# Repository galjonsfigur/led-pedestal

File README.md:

# LED Pedestal

This repository contains hardware, firmware and
3D-printable case for the LED Pedestal project.

## What is this project?

The name says it all - it's just a fancy-looking circuit
that can blink your precious (retro or not) LED that you probably
still keep at the bottom of your component drawer. The circuit is heavily
over-complicated and the same thing could be done using 3 or 4 components total,
but it looks cool and has some nice features:

- PIC10F222 micro controller with sophisticated firmware (as far as 512 bytes 
firmware written in C with some assembly can be)
- Whole 3 (three!) randomly-parameterized LED effects to select from 
- Micro USB for charging the Li-Ion battery with all the (unnecessary)
protection circuits (overcharge, over-discharge and short-circuit protection) 
- small button for checking battery level and changing LED Blinking modes
- reaction to connecting charger and showing charging status
- can work while charging from USB

And on top of that, cool-looking glass dome case 
to encapsulate the spirit of your LED!

## How do I make my own?

Before you start you have to:

- be able to solder small SMD components (TSSOP-8 is the smallest-pitch used in
the design) and use hot-air or hot plate (or frying pan) to solder
micro USB port (you could try to use soldering iron but it will be much more 
tedious) 
- be able to program PIC10F222 micro controller (even cheap PICKit2 can be used)
- calculate current-limiting resistor for your LED assuming 3.3V drive voltage,
voltage drop and recommended current from LED datasheet. You can calculate it
using the following formula: `R = (V_battery - V_LEDdrop) / I_LED` or just slam
68 Ohm one and call it a day 

You can use available [gerber zip](hardware/gerbers_v2.zip) archive and order
the PCB from your favorite (or the cheapest) PCB manufacturer and buy the 
necessary components listed in the Bill of materials (most of them should be
cheap and easy to obtain even from places like AliExpress).

Bill of materials can be found [here.](bom.txt)

#### Assembly of the PCB

If you are soldering the PCB by hand, begin with USB port and the button 
Jumper from middle pad to pad marked with an arrow is variant with Random 
Seed Generator (Not implemented) and the jumper from middle pad to the 
third one (the one without arrow mark) is variant with battery 
measurement - connected by default in revision 2 of PCB, so if by any chance
you uploaded `gerbers_v1` instead of `gerbers_v2` you will have to solder it.
If your precious LED still has long legs don't cut them and instead solder it to
be as high above the PCB as possible! Cathode is the square pad. After soldering
SMD components solder trough-hole JST socket or the Li-ion cell directly.

If for whatever reason don't want to use 
[SOICBite](https://github.com/SimonMerrett/SOICbite) you can solder wires to the
pads directly and connect it to the programmer or program the PIC before
soldering it. Connection diagram can be found in the schematic and programming 
pads description in `media` folder). Example programming jig:

After connecting the Li-Ion cell you have to connect it to the USB
to start the protection circuits (they go to fail-save mode if the battery was
disconnected) and you should have a nice and working pedestal!

#### Assembling the case

To assemble the case you will need following elements:

- three 3D-printed parts - STL files are in `case` folder. I recommend to print
them with some nice material and fine settings - they should look better than
your average print!
- eight round 2x2mm N35 magnets
- 12x18mm glass dome

You should be able to get those on AliExpress or similar sites. 
Glue 3D-printed ring to the bottom of glass dome and put the magnets
into the holes in such configuration that two case parts attract each 
other. then put the PCB and the battery into the bottom part, the glass dome
into the upper one and they should snap together. 

## Battery life
On 35mAh Li-ion 3.7V battery it should work:

- about 20 hours when in random blink mode
- about 15 hours when in both breathing modes
- much longer when in shutdown mode (PIC has to wake up every ~2 seconds just to
go to sleep again)

It mostly depends on the LED used as the firmware does everything it can
to preserve battery life.

## More pictures?

Gallery can be found in `media` folder if you like even more photos and videos
of this thingy.

## How do I use this?

If you click the button, the device will blink out it's status:

- if connected to charger
	- two short blinks means that it's charged
	- two slightly longer blinks means that its still charging
- if working from battery
	- from 6 to 2 blinks that indicate battery level - more blinks means more
	battery left
	- one short blink means battery is almost empty
	- no blinks means it's dead and you should connect it to USB

To change blinking mode, you have to press the button until LED will make a long
blink - that means it changed mode. If you don't release the button the 
mode will keep changing to next one on list bellow with each long blink. 

Implemented modes (whole four!):

- Random LED blink
- Sine-like LED breathing
- Linear LED breathing
- Power-off

### What else can/could be done:
The project is functional as-it-is but there is some room for improvements for
the software (hardware-wise it probably would be better to just connect it 
to Digispark and call it a day):

- Test other effects than RNG-BLINKENKIGHT, Quadwave and Triwave fading - simple
"test jig" can be found in `effects-workdir` folder.
- Try to rewrite current `quadwave` effect as it's not well suited 
for the PIC core
- Think of better effects that could be implemented given so little space

### Differences between PCB versions:

- change of some component values to reduce number of different resistor values
- more silkscreen markings on new PCB
- bigger pads on the button footprint (previous were hard to solder
  without hot plate) 
- the button is now closer to the PCB center - better fit with the case

## Author ramblings about the design

This whole project started because of the one small LED found in old lab
equipment and most of the decisions weren't really well-thought - after all
it wasn't meant to be some mass-produced product (if you want thing like that
you could just buy electronic candle) and, as always, only after the fact 
better ideas start popping in one's head. Bellow are some of them:

- Using other SOT-23 micro controller would probably allow for more effects and
slightly better battery life - for example PIC0F322 or Padauk PMS150C-U06 
or ATiny10, but I had access only to PIC10F222 so I used those. If someone would
want to port this firmware to other micro it should be possible - it's (almost)
C after all. I wanted to use SOT-23 as much as possible because it's small but
still fairly easy to solder, but there are many other options.
- Whole battery protection circuit could be ditched as even small Li-ion cell
come with one or at least change FS8205A to SOT-23 version that is smaller 
and easier to solder.
- Some elements around the button pin could be probably removed (they were there
because at design time it was undecided if this pedestal should work only 
on button press or the button would control the mode. Now those elements
function as over-complicated debouncing circuit. 
- author thought on the idea to make random seed generator based on
fluctuations of RC time constant where instead of resistor, a thermistor would
be used. But as it turned out, 16-bit LSFR was sufficient and showing battery
level seemed more useful in this useless device. If the capacitor will be
charged and pin function would be switched to ADC, the voltage level would
depend only on R value that is dependent on temperature. But on 8-bit fixed
sampling time ADC the variation wouldn't be too big(if any) so multiple readings
would be needed to extract any entropy from it.

## License
BSD 3-Clause

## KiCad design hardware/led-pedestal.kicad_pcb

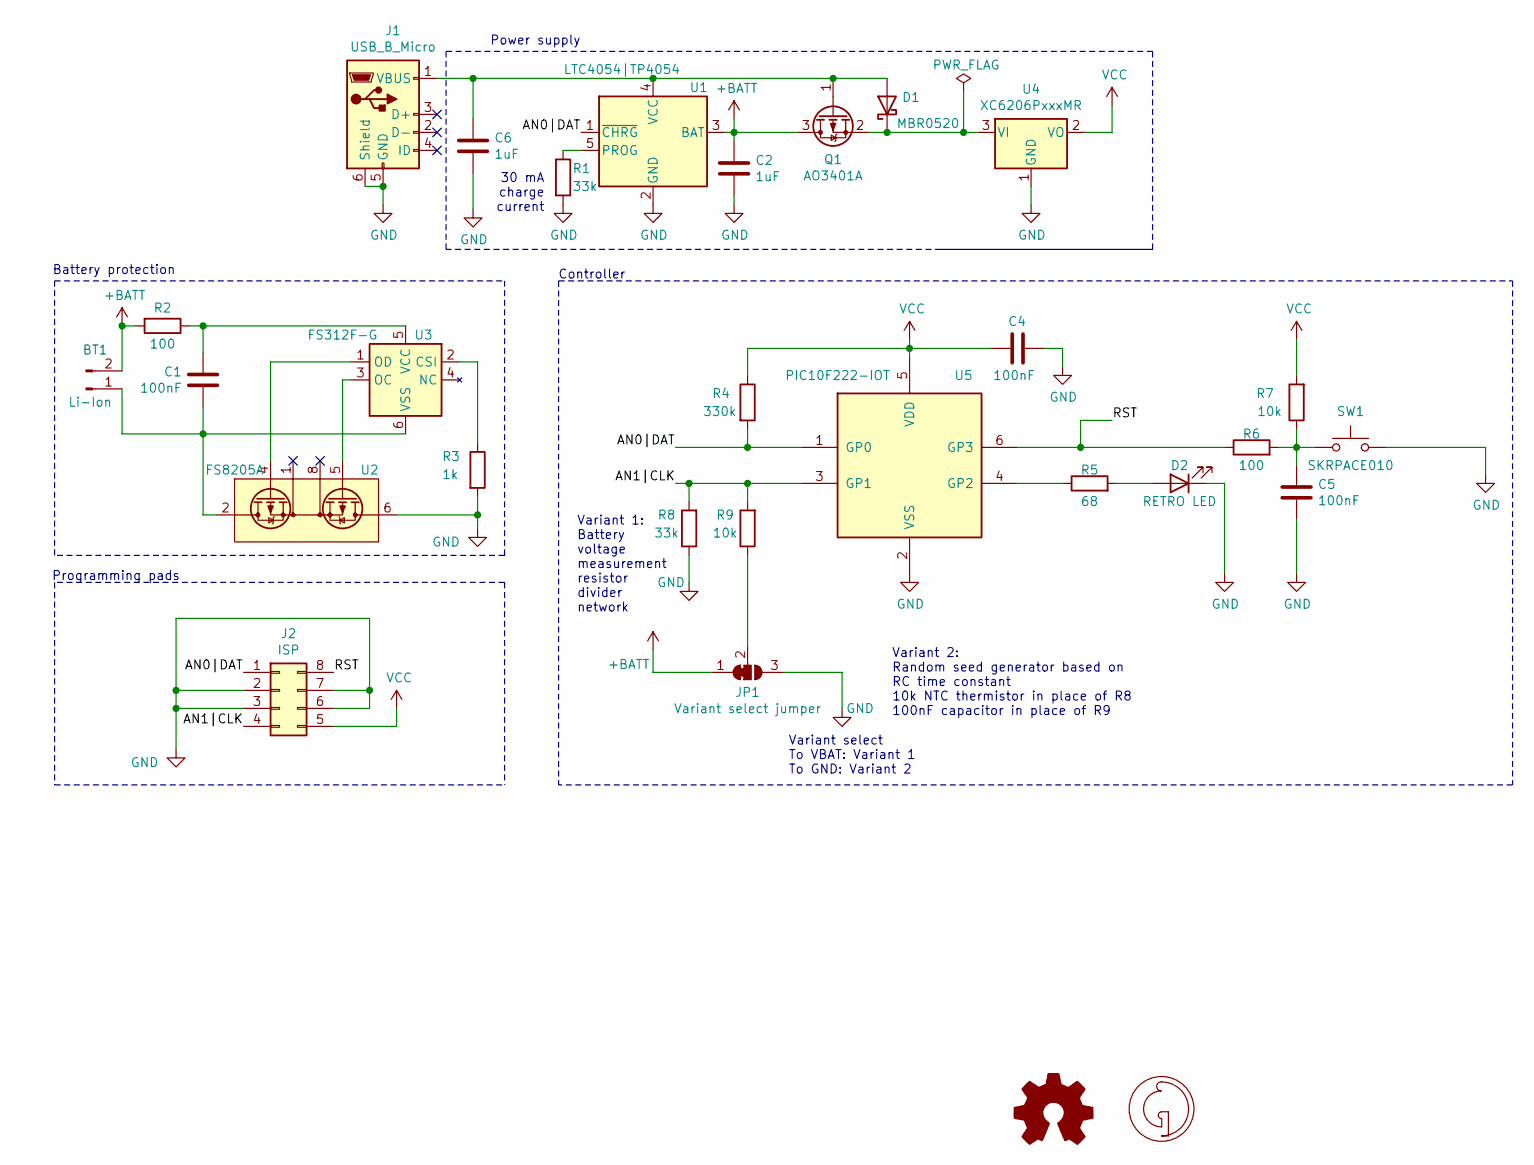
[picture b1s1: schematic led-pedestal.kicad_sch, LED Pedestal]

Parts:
BT1: Li-Ion; JST_PH_B2B-PH-K_1x02_P2.00mm_Vertical
C1, C4, C5: 100nF; C_0805_2012Metric_Pad1.18x1.45mm_HandSolder
C2, C6: 1uF; C_0805_2012Metric_Pad1.18x1.45mm_HandSolder
D1: MBR0520; D_SOD-123
D2: RETRO LED; LED_D3.0mm_FlatTop
J1: USB_B_Micro; USB_Micro-B_Molex_47346-0001
J2: ISP; SOIC_clipProgSmall
JP1: Variant select jumper; SolderJumper-3_P1.3mm_Bridged12_RoundedPad1.0x1.5mm_NumberL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
LG1: Galion_Logo; Galion_Logo_Small
LG2: Logo_Open_Hardware_Small; OSHW-Symbol_6.7x6mm_SilkScreen
Q1: AO3401A; SOT-23
R1, R8: 33k; R_0805_2012Metric_Pad1.20x1.40mm_HandSolder
R2, R6: 100; R_0805_2012Metric_Pad1.20x1.40mm_HandSolder
R3: 1k; R_0805_2012Metric_Pad1.20x1.40mm_HandSolder
R4: 330k; R_0805_2012Metric_Pad1.20x1.40mm_HandSolder
R5: 68; R_0805_2012Metric_Pad1.20x1.40mm_HandSolder
R7, R9: 10k; R_0805_2012Metric_Pad1.20x1.40mm_HandSolder
SW1: SKRPACE010
U1: LTC4054|TP4054; TSOT-23-5
U2: FS8205A; TSSOP-8_4.4x3mm_P0.65mm
U3: FS312F-G; SOT-23-6
U4: XC6206PxxxMR; SOT-23
U5: PIC10F222-IOT; SOT-23-6

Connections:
+BATT: BT1.2, C2.1, JP1.1 (A), Q1.3 (D), R2.2, U1.3 (BAT)
/AN0|DAT: J2.1, R4.2, U1.1 (~CHRG), U5.1 (GP0)
/AN1|CLK: J2.4, R8.2, R9.2, U5.3 (GP1)
/RST: J2.8, R6.1, U5.6 (GP3)
GND: C2.2, C4.2, C5.2, C6.2, D2.1 (K), J1.5 (GND), J1.6 (Shield), J2.2, J2.3, J2.6, J2.7, JP1.3 (B), R1.2, R3.2, R8.1, SW1.3, SW1.4, U1.2 (GND), U2.6 (S2), U2.7 (S2), U4.1 (GND), U5.2 (VSS)
unnamed: BT1.1, C1.2, U2.2 (S1), U2.3 (S1), U3.6 (VSS)
unnamed: C1.1, R2.1, U3.5 (VCC)
unnamed: C5.1, R6.2, R7.1, SW1.1, SW1.2
unnamed: C6.1, D1.2 (A), J1.1 (VBUS), Q1.1 (G), U1.4 (VCC)
unnamed: D1.1 (K), Q1.2 (S), U4.3 (VI)
unnamed: D2.2 (A), R5.2
unnamed: JP1.2 (C), R9.1
unnamed: R1.1, U1.5 (PROG)
unnamed: R3.1, U3.2 (CSI)
unnamed: R5.1, U5.4 (GP2)
unnamed: U2.4 (G1), U3.1 (OD)
unnamed: U2.5 (G2), U3.3 (OC)
VCC: C4.1, J2.5, R4.1, R7.2, U4.2 (VO), U5.5 (VDD)

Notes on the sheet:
Battery protection
Programming pads
30 mA charge current
Variant 1: Battery voltage measurement resistor divider network
Power supply
Controller
Variant select To VBAT: Variant 1 To GND: Variant 2
Variant 2: Random seed generator based on RC time constant 10k NTC thermistor in place of R8 100nF capacitor in place of R9

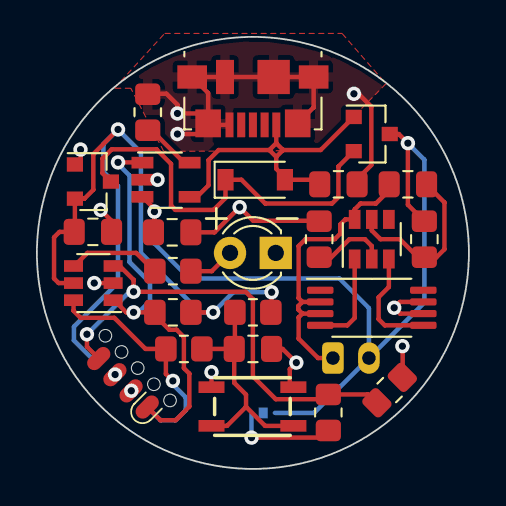
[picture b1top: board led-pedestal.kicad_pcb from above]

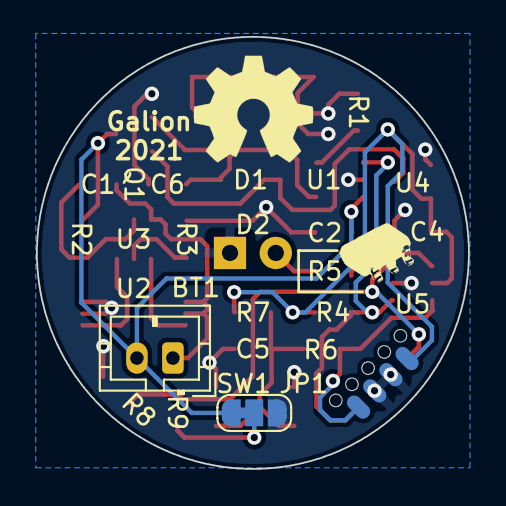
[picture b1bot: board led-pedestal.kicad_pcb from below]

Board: 2 copper layers, 24.0 x 24.0 mm, 29 parts (4 on the bottom side), 18 nets.

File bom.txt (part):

+--------------------+--------------------------+---------------------------------------------------------------+----------------------------------------------------------------------------------+
| Ref                | Value                    | Footprint                                                     | Datasheet                                                                        |
+--------------------+--------------------------+---------------------------------------------------------------+----------------------------------------------------------------------------------+
| BT1                | Li-Ion                   | Connector_JST:JST_PH_B2B-PH-K_1x02_P2.00mm_Vertical           | ~                                                                                |
+--------------------+--------------------------+---------------------------------------------------------------+----------------------------------------------------------------------------------+
| C1                 | 100nF                    | Capacitor_SMD:C_0805_2012Metric_Pad1.18x1.45mm_HandSolder     | ~                                                                                |
+--------------------+--------------------------+---------------------------------------------------------------+----------------------------------------------------------------------------------+
| C2                 | 1uF                      | Capacitor_SMD:C_0805_2012Metric_Pad1.18x1.45mm_HandSolder     | ~                                                                                |
+--------------------+--------------------------+---------------------------------------------------------------+----------------------------------------------------------------------------------+
| C4                 | 100nF                    | Capacitor_SMD:C_0805_2012Metric_Pad1.18x1.45mm_HandSolder     | ~                                                                                |
+--------------------+--------------------------+---------------------------------------------------------------+----------------------------------------------------------------------------------+
| C5                 | 100nF                    | Capacitor_SMD:C_0805_2012Metric_Pad1.18x1.45mm_HandSolder     | ~                                                                                |
+--------------------+--------------------------+---------------------------------------------------------------+----------------------------------------------------------------------------------+
| C6                 | 1uF                      | Capacitor_SMD:C_0805_2012Metric_Pad1.18x1.45mm_HandSolder     | ~                                                                                |
+--------------------+--------------------------+---------------------------------------------------------------+----------------------------------------------------------------------------------+
| D1                 | MBR0520                  | Diode_SMD:D_SOD-123                                           | http://www.mccsemi.com/up_pdf/MBR0520~MBR0580(SOD123).pdf                        |
+--------------------+--------------------------+---------------------------------------------------------------+----------------------------------------------------------------------------------+
| D2                 | RETRO LED                | LED_THT:LED_D3.0mm_FlatTop                                    | ~                                                                                |
+--------------------+--------------------------+---------------------------------------------------------------+----------------------------------------------------------------------------------+
| J1                 | USB_B_Micro              | Connector_USB:USB_Micro-B_Molex_47346-0001                    | ~                                                                                |
+--------------------+--------------------------+---------------------------------------------------------------+----------------------------------------------------------------------------------+
| Q1                 | AO3401A                  | Package_TO_SOT_SMD:SOT-23                                     | http://www.aosmd.com/pdfs/datasheet/AO3401A.pdf                                  |
+--------------------+--------------------------+---------------------------------------------------------------+----------------------------------------------------------------------------------+
| R1                 | 33k                      | Resistor_SMD:R_0805_2012Metric_Pad1.20x1.40mm_HandSolder      | ~                                                                                |
+--------------------+--------------------------+---------------------------------------------------------------+----------------------------------------------------------------------------------+
| R2                 | 100                      | Resistor_SMD:R_0805_2012Metric_Pad1.20x1.40mm_HandSolder      | ~                                                                                |
+--------------------+--------------------------+---------------------------------------------------------------+----------------------------------------------------------------------------------+
| R3                 | 1k                       | Resistor_SMD:R_0805_2012Metric_Pad1.20x1.40mm_HandSolder      | ~                                                                                |
+--------------------+--------------------------+---------------------------------------------------------------+----------------------------------------------------------------------------------+
| R4                 | 330k                     | Resistor_SMD:R_0805_2012Metric_Pad1.20x1.40mm_HandSolder      | ~                                                                                |
+--------------------+--------------------------+---------------------------------------------------------------+----------------------------------------------------------------------------------+
| R5                 | 68                       | Resistor_SMD:R_0805_2012Metric_Pad1.20x1.40mm_HandSolder      | ~                                                                                |
+--------------------+--------------------------+---------------------------------------------------------------+----------------------------------------------------------------------------------+
| R6                 | 100                      | Resistor_SMD:R_0805_2012Metric_Pad1.20x1.40mm_HandSolder      | ~                                                                                |
+--------------------+--------------------------+---------------------------------------------------------------+----------------------------------------------------------------------------------+
| R7                 | 10k                      | Resistor_SMD:R_0805_2012Metric_Pad1.20x1.40mm_HandSolder      | ~                                                                                |
+--------------------+--------------------------+---------------------------------------------------------------+----------------------------------------------------------------------------------+
| R8                 | 33k                      | Resistor_SMD:R_0805_2012Metric_Pad1.20x1.40mm_HandSolder      | ~                                                                                |
+--------------------+--------------------------+---------------------------------------------------------------+----------------------------------------------------------------------------------+
| R9                 | 10k                      | Resistor_SMD:R_0805_2012Metric_Pad1.20x1.40mm_HandSolder      | ~                                                                                |
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
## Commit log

2021-04-12 Add revision 2 of the hardware
    Changes include:
    - moved button to the center for better fit of the case
    - added silkscreen marks for + and minus of the LED
    - connect jumper to battery measurement variant
    - lower charging current (from 100 to 30 mA)
2021-07-11 Re-export correct files for revision 2 of the PCB
2021-07-11 Add case files with holes for magnets
2021-07-11 Update documentation and add more photos
2021-07-11 Squeeze some bytes to get more gradual battery levels to show
2021-07-12 Add .gitattributes to fix GitHub statistics
